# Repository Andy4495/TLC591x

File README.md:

# TLC591x Library

This library is designed to interface with the Texas Instruments [TLC5916 and TLC5917 8-Channel Constant-Current LED Sink Drivers][1].

A minimum of three I/O pins are required (SDI, CLK, LE). An optional fourth pin can be defined for the output enable signal (/OE). If not used, the library assumes that the pin is tied low (and the LED output is always enabled). The /OE pin is required if you want to switch the chip to Special Mode.

This library can use either a processor's built-in hardware SPI interface (by way of the Arduino SPI library), or a software serial interface which allows just about any I/O pin to be used to control the TLC591x chip.

Up to 254 TLC591x chips can be cascaded together to control various LED configurations: LED bar graph, common anode 7-segment displays, or individual LEDs.

## Usage

*See the sketches included in the `examples` folder.*

1. Include the header file:

    ```cpp
    #include <TLC591x.h>
    ```

2. Use a constructor to create an LED object:

    - For software SPI, use one of the following:

    ```cpp
    TLC591x myLED(num_chips, SDI_pin, CLK_pin, LE_pin, OE_pin);  // OE pin controlled by library
    TLC591x myLED(num_chips, SDI_pin, CLK_pin, LE_pin);          // OE pin hard-wired low (always enabled)
    ```

   - For hardware SPI, use one of the following:

    ```cpp
    TLC591x myLED(num_chips, LE_pin, OE_pin);  // OE pin controlled by library
    TLC591x myLED(num_chips, LE_pin);          // OE pin hard-wired low (always enabled)
    ```

    The `num_chips` parameter defines how many chips are cascaded together (maximum of 254). The chips include a serial data output (SDO) pin so that several chips can be connected in a daisy-chain configuration.

    If using the /OE pin, the default state is for the display to be turned off, so the `enableDisplay()` method needs to be called to turn on the display after powering up.

3. Once you have created a TLC591x object, the following methods can be used to control the LEDs.

- Print ASCII characters to 7-segment displays:

   ```cpp
   void print(char* s)
   ```

   `s` is a char array with a size of at least `num_chips` containing ASCII characters. It is similar to a c-string but does not need to be null-terminated since its size is assumed to be `num_chips` as defined in the constructor. Any characters beyond the number of chips defined in the constructor are ignored.

   The most significant digit is in element 0 of the array.

   The library includes a pre-defined mapping for displaying ASCII characters (letters, numbers, symbols) from 32 - 127 and assumes that the TLC591x chip is connected to the 7-segment display as follows:

   ```text
   TLC591x Pin  Display Segment
   -----------  ---------------
      OUT0            DP
      OUT1             A
      OUT2             B
      OUT3             C
      OUT4             E
      OUT5             G
      OUT6             F
      OUT7             D
   ```

   Note that a 7-segment display does not allow an accurate rendering of all ASCII characters and symbols.

- To control individual LEDs:

   ```cpp
    void print(unsigned int n)
   ```

   The value `n` is shifted out to the TLC591x chip(s) one bit at a time. If a single-chip configuration was defined in the constructor, then only the least-significant 8 bits are shifted.

   *This method only supports one or two TLC591x chips, and is included for backward compatibility with older versions of the library. If you are using more than two chips, then use `printDirect()` instead.*

- To control individual LEDs, or directly control LED segments in a 7-segment display, use:

   ```cpp
    void printDirect(const uint8_t* b)
   ```

   `b` is an array of size of at least `num_chips`. The values are shifted out right to left (i.e., `b[0]` is shifed out last).

- Control the output enable (/OE) signal. These methods only have an effect if the OE pin was defined in the constructor. Also, they override the brightness setting of `displayBrightness()`.

   ```cpp
   void displayEnable();
   ```

   Sets the output enable (/OE) signal low, which turns on the display. The default state of the /OE pin when defined in the constructor is disabled.

   ```cpp
    void displayDisable();  
   ```

   Sets the output enable (/OE) signal high, which turns off the display.  

- To put the TLC591x chip into Normal Mode (see [datasheet][1] for more info). This method overrides the brightness setting of `displayBrightness()`:

   ```cpp
   void normalMode();
   ```

   The chip is in normal mode by default when powered on.

- To put the TLC591x chip into Special Mode (see [datasheet][1] for more info). This method overrides the brightness setting of `displayBrightness()`:

   ```cpp
   void specialMode();
   ```

   The chip must have the /OE signal connected to the microcontroller (and defined in the constructor) for this method to have an effect. While in Special Mode, the display is disabled. Once the chip is in special mode, the Configuration Latch can be written using the printDirect() method.

- To conntrol the display brightness:

   ```cpp
   void displayBrightness(byte b);
   ```

   Uses PWM on /OE pin to control display brightness. This method requires that the /OE pin is a PWM-capable pin and is defined in the constructor. Note that since /OE is active low, a value of zero is brightest and 255 is dimmest.

   This method enables the display, so that if the display was previously disabled with `displayDisable()`, the display will be turned on. The brightness setting is overwritten by any of the following methods: `enableDisplay()`, `disableDisplay()`, `normalMode()`, `specialMode()`.

   This command should only be used while the display is in normal mode. Unexpected results may occur if this method is called while in special mode.

## Hardware Design

A reference design incorporating two TLC5916/7 chips and various LEDs configurations is available in the [extras/hardware][2] folder.

## Hardware and Software SPI Compatibility

The library has been tested with AVR, MSP430, MSP432, and Tiva processors using both hardware and software SPI.

When configured to use software SPI, this library should work with any processor that is supported by the Arduino IDE, because it uses platform-agnostic `digitalWrite()` functions to control the hardware.

While the library has been tested with the hardware platforms listed above, there could potentially be compatibility issues with other platforms when using hardware SPI.

## References

- [TLC591x datasheet][1]

## License

The software and other files in this repository are released under what is commonly called the [MIT License][100]. See the file [`LICENSE.txt`][101] in this repository.

[1]: http://www.ti.com/lit/ds/symlink/tlc5916.pdf
[2]: ./extras/hardware
[100]: https://choosealicense.com/licenses/mit/
[101]: ./LICENSE.txt
[//]: # ([200]: https://github.com/Andy4495/TLC591x)

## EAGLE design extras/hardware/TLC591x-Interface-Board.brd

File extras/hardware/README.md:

# TLC591x Interface Board

The `extras/hardware` folder contains a reference design (schematic and PCB) that can be used with the TLC591x library.

The design uses two [TLC5916/7 driver chips][2] and can support a 10-segment bar graph, 16 individual LEDs, or a 2-digit 7-segment common anode LED display. Any 7-segment display that has a pinout compatible with the HP/Avago/Broadcom [HDSP-K511][1]should work with this design.

The TLC591x chip has an internal pull-down for the LE signal and an internal pull-up for the /OE signal, so neither signal is left floating at powerup.

The circuit has a jumper for the /OE signal so that it can be hard-wired to Vcc or the signal can be under software control from the microcontroller.

The SDO signal is available on the signal header to allow daisy-chaining additional modules.

The design allows for separate VLED and Vcc supplies, or they can be tied together with jumpers for single supply operation.

There are multiple positions to place resistors for R-EXT to control the display current -- this is to allow more easily changing external resistor values by placing a new resistor either in parallel with an existing resistor or clipping the old resistor without having to unsolder parts.

## References

+ TLC5916/7 [datasheet][2].
+ HDSP-K511 7-segment display [datasheet][1].

## License

The software and other files in this repository are released under what is commonly called the [MIT License][100]. See the file [`LICENSE.txt`][101] in this repository.

[1]: https://docs.broadcom.com/docs/AV02-2555EN
[2]: http://www.ti.com/lit/ds/symlink/tlc5916.pdf
[100]: https://choosealicense.com/licenses/mit/
[101]: ../../LICENSE.txt
[//]: # ([200]: https://github.com/Andy4495/TLC591x)

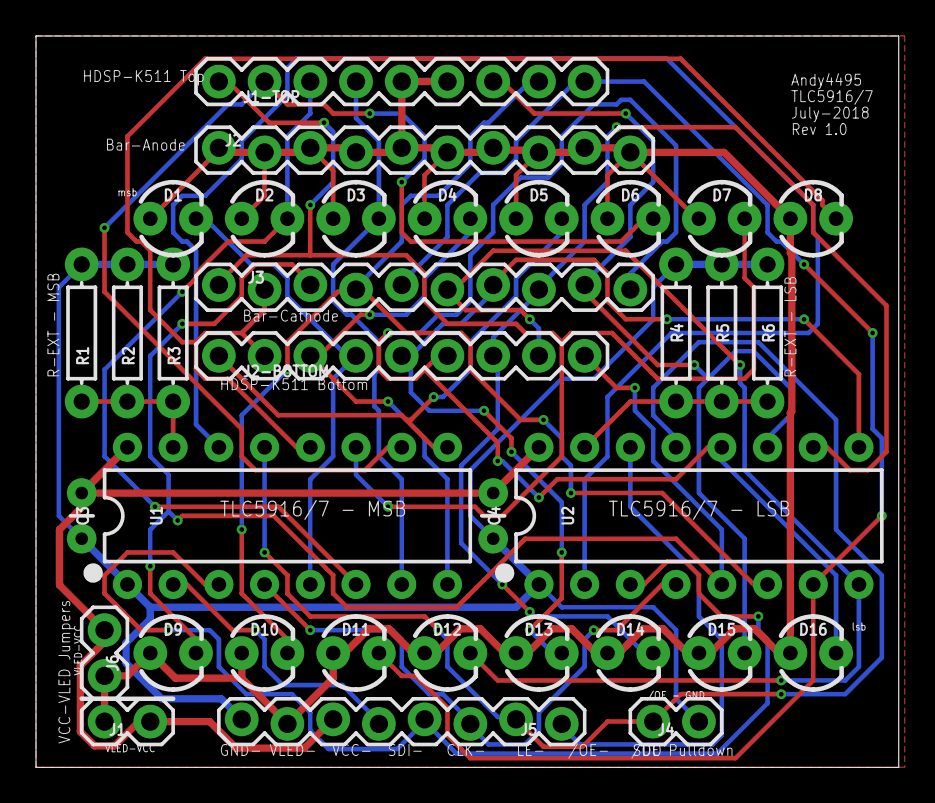
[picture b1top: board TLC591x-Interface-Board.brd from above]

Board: 2 copper layers, 47.9 x 40.6 mm, 34 parts (0 on the bottom side), 27 nets.

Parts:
C3, C4: 22pF; CAP-PTH-2.54
D1, D2, D3, D4, D5, D6, D7, D8, D9, D10, D11, D12, D13, D14, D15, D16: LED_3MM
J1, J4, J6: 1X02
J1-TOP, J2-BOTTOM: 1X09
J2, J3: 1X10_LOCK
J5: 1X08_LOCK
R1, R2, R3, R4, R5, R6: 1k; AXIAL-0.3
U1, U2: TLC5916/7; DIP16

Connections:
GND: C3.2, C4.2, J4.1, J5.8, R1.P$1, R2.P$1, R3.P$1, R4.P$1, R5.P$1, R6.P$1, U1.1, U2.1
unnamed: J4.2, J5.2, U1.13, U2.13
unnamed: J5.1, U2.14
unnamed: D15.K, J1-TOP.7, J3.9, U2.11
unnamed: D7.K, J1-TOP.1, J3.1, U1.11
unnamed: D6.K, J1-TOP.2, U1.10
unnamed: D5.K, J2-BOTTOM.1, U1.9
unnamed: D4.K, J2-BOTTOM.3, U1.8
unnamed: D3.K, J1-TOP.4, U1.7
unnamed: D2.K, J1-TOP.3, U1.6
unnamed: D1.K, J2-BOTTOM.4, U1.5
unnamed: D16.K, J2-BOTTOM.6, J3.10, U2.12
unnamed: D14.K, J2-BOTTOM.7, J3.8, U2.10
unnamed: D13.K, J2-BOTTOM.5, J3.7, U2.9
unnamed: D12.K, J2-BOTTOM.8, J3.6, U2.8
unnamed: D11.K, J1-TOP.9, J3.5, U2.7
unnamed: D10.K, J1-TOP.8, J3.4, U2.6
unnamed: D9.K, J2-BOTTOM.9, J3.3, U2.5
unnamed: R1.P$2, R2.P$2, R3.P$2, U1.15
unnamed: U1.14, U2.2
unnamed: R4.P$2, R5.P$2, R6.P$2, U2.15
unnamed: J5.5, U1.2
unnamed: J5.4, U1.3, U2.3
unnamed: J5.3, U1.4, U2.4
unnamed: D8.K, J2-BOTTOM.2, J3.2, U1.12
VCC: C3.1, C4.1, J1.1, J5.6, J6.1, U1.16, U2.16
VCC_1: D1.A, D2.A, D3.A, D4.A, D5.A, D6.A, D7.A, D8.A, D9.A, D10.A, D11.A, D12.A, D13.A, D14.A, D15.A, D16.A, J1.2, J1-TOP.5, J1-TOP.6, J2.1, J2.2, J2.3, J2.4, J2.5, J2.6, J2.7, J2.8, J2.9, J2.10, J5.7, J6.2

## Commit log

2018-08-06 Initial commit.
2018-08-06 fix typo in library properties.
2018-08-06 Change parameter to signed instead of unsigned.
2018-08-07 Add hadware reference design.
2018-08-07 Fix URL.
2018-08-07 Fix minor typos.
2018-12-02 fix msp430 architecture in library.properties
2019-11-15 Update gitlab references to github.
2019-11-15 Update version since repository URL changed.
2020-01-08 Update arch property.
2020-01-08 Update sentence property.
2020-01-09 Re-arrange file structure to put hardware folder under extras.
2020-09-25 Array bound error, fixes #1.
2020-09-25 Support up 254 chips: fixes #2.
2020-09-25 Update library version.
2021-01-18 Add new methods specialMode() and normalMode().
2021-01-18 Add displayBrightness() method (uses PWM).
2021-01-23 Update example to include new methods.
2021-04-14 Add license info.
2021-05-01 Clean up markdownlint issues.
2022-02-25 Add .gitignore
2022-03-21 Add workflows
2022-06-27 Fix URL, update to 1.1.3
2022-07-12 Add arduino lint workflow
2022-07-29 Add build matrix avr, msp
2022-08-20 Add Arduino lint badge
2022-08-31 Add hardware SPI support
2022-09-02 Updates after testing. Fixes #3.
2022-09-02 Clarify compatibiliy
2022-09-02 Update to support hardware SPI on msp432r, tivac
2022-09-06 Updates for tivac and msp432r
2022-09-08 markdownlint issues
2022-09-09 Fix #4 msp432r and tivac, fix pwm-spcl mode race
2022-09-09 Update with 1.4.0 changes
2022-10-03 Update for nektos/act compatibility
2022-10-10 Bump actions/checkout from 2 to 3.1.0
    Bumps [actions/checkout](https://github.com/actions/checkout) from 2 to 3.1.0.
    - [Release notes](https://github.com/actions/checkout/releases)
    - [Changelog](https://github.com/actions/checkout/blob/main/CHANGELOG.md)
    - [Commits](https://github.com/actions/checkout/compare/v2...v3.1.0)
    ---
    updated-dependencies:
2022-10-11 Bump actions/checkout from 2 to 3.1.0 (#5)
    * Bump actions/checkout from 2 to 3.1.0
    Bumps [actions/checkout](https://github.com/actions/checkout) from 2 to 3.1.0.
    - [Release notes](https://github.com/actions/checkout/releases)
    - [Changelog](https://github.com/actions/checkout/blob/main/CHANGELOG.md)
    - [Commits](https://github.com/actions/checkout/compare/v2...v3.1.0)
    ---
2023-08-02 Java no longer needed with msp432 5.29.4
2023-08-02 Change - to _ in name to fix compilation issue (may be related to https://github.com/energia/msp432-core/issues/47)
2023-08-31 nektos/act compatibility
2023-09-05 Change to reusable workflows
2023-09-14 Fixes #6 - compile errors with esp32
2023-09-15 Add stm32 platform to compile-sketches
2023-09-17 Add create-release workflow
2024-03-08 Update cron time
2024-09-27 Use new Package Index JSON Files
2024-09-27 Update msp432 checks
2024-09-30 Switch to lychee for link checks
2024-10-01 add extra-input-files to catch all the .md files
2024-10-01 ./extras/**/*.md is now included in base action
2024-10-07 Comment out extra toggleLE() call in HW SPI
2024-10-07 Remove extra call to toggleLE() in hardware SPI mode
2024-10-07 Remove extra call to toggleLE() in HW SPI mode (fixes #8) (#9)
    * Remove extra call to toggleLE() in hardware SPI mode
2025-01-03 Add GCC9 to compile matrix

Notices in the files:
parts and their libraries:
SparkFun-Connectors: Licensing: Creative Commons ShareAlike 4.0 International - https://creativecommons.org/licenses/by-sa/4.0
